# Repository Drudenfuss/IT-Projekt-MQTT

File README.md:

# IT-Projekt-MQTT
BZTG Oldenburg ETS 1. IT- Projekt MQTT Controller.

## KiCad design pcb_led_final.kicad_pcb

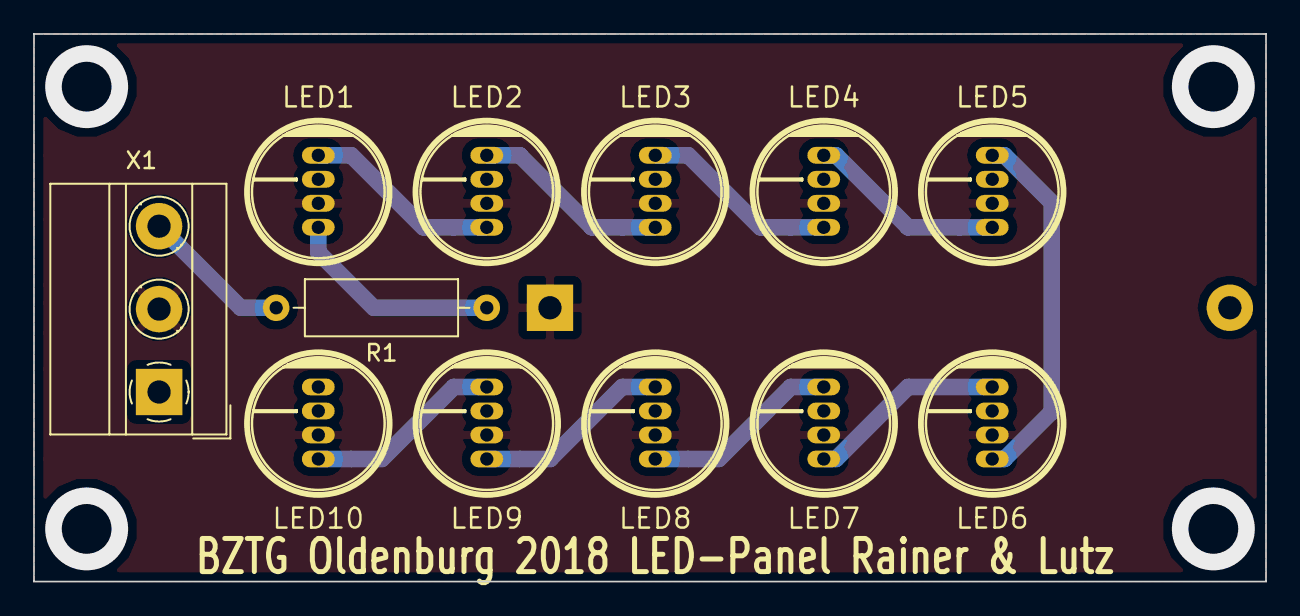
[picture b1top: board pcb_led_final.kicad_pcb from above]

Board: 2 copper layers, 74.3 x 33.0 mm, 13 parts (1 on the bottom side), 13 nets.

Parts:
C1: CP; CP_Axial_L34.5mm_D20.0mm_P41.00mm_Horizontal
LED1, LED2, LED3, LED4, LED5, LED6, LED7, LED8, LED9, LED10: WS2811; PL9823-SYSMATT-V4
R1: 220_Ohm; R_Axial_DIN0309_L9.0mm_D3.2mm_P12.70mm_Horizontal
X1: LED Terminal; TerminalBlock_MetzConnect_Type011_RT05503HBWC_1x03_P5.00mm_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

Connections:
/3.3V_VCC: C1.1, LED1.2, LED2.2, LED3.2, LED4.2, LED5.2, LED6.2, LED7.2, LED8.2, LED9.2, LED10.2, X1.2
/GND: C1.2, LED1.3, LED2.3, LED3.3, LED4.3, LED5.3, LED6.3, LED7.3, LED8.3, LED9.3, LED10.3, X1.1
unnamed: LED1.1, R1.1
unnamed: LED1.4, LED2.1
unnamed: LED2.4, LED3.1
unnamed: LED3.4, LED4.1
unnamed: LED4.4, LED5.1
unnamed: LED5.4, LED6.1
unnamed: LED6.4, LED7.1
unnamed: LED7.4, LED8.1
unnamed: LED8.4, LED9.1
unnamed: LED9.4, LED10.1
unnamed: R1.2, X1.3

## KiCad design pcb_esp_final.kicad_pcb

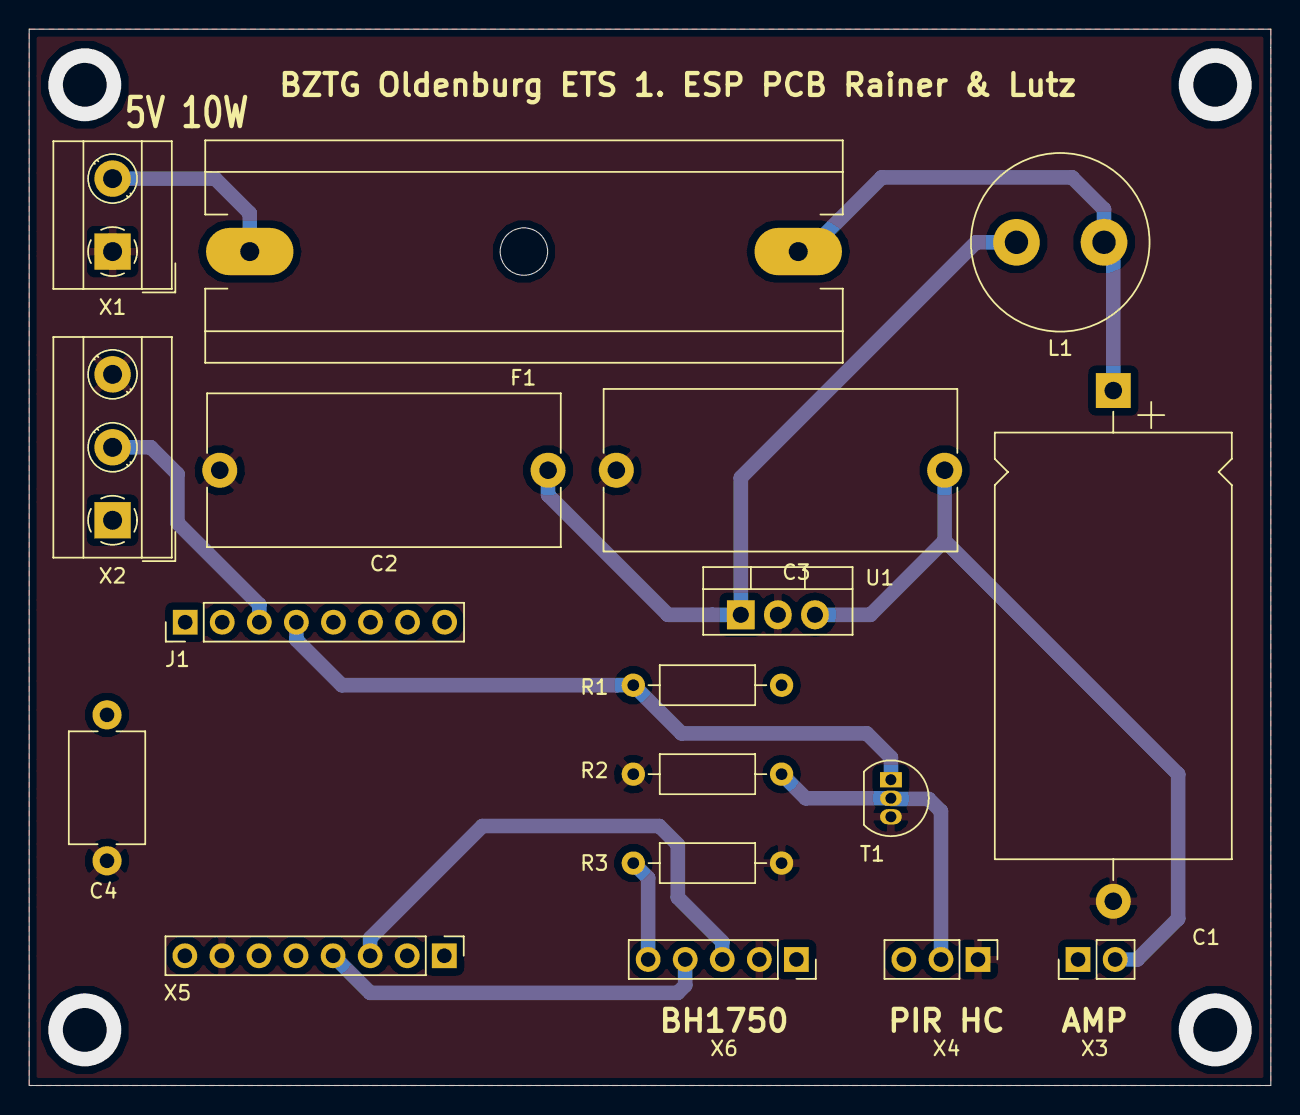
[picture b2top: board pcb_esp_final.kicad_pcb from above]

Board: 2 copper layers, 85.1 x 72.4 mm, 18 parts (0 on the bottom side), 12 nets.

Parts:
C1: 4,7 μF; CP_Axial_L29.0mm_D16.0mm_P35.00mm_Horizontal
C2: 10 μF; C_Rect_L24.0mm_W10.3mm_P22.50mm_MKT
C3: 22 μF; C_Rect_L24.0mm_W10.9mm_P22.50mm_MKT
C4: 100 nF; C_Disc_D7.5mm_W5.0mm_P10.00mm
F1: 3A_Mittelträge; Fuseholder_Cylinder-5x20mm_Schurter_0031-8002_Horizontal_Op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
J1: Conn_01x08_Male; PinHeader_1x08_P2.54mm_Vertical
L1: 12 μH; L_Radial_D12.0mm_P6.00mm_MuRATA_1900R
R1: 10K; R_Axial_DIN0207_L6.3mm_D2.5mm_P10.16mm_Horizontal
R2: 5K; R_Axial_DIN0207_L6.3mm_D2.5mm_P10.16mm_Horizontal
R3: 1K; R_Axial_DIN0207_L6.3mm_D2.5mm_P10.16mm_Horizontal
T1: BC413; TO-92_Inline
U1: AMSR01-783.3-NZ 3.3V; TO-220-3_Vertical
X1: USB_VCC; TerminalBlock_MetzConnect_Type055_RT01502HDWU_1x02_P5.00mm_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
X2: LED_Panel; TerminalBlock_MetzConnect_Type055_RT01503HDWU_1x03_P5.00mm_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
X3: Strommessung; PinHeader_1x02_P2.54mm_Vertical
X4: PIR-HC-SR501; PinHeader_1x03_P2.54mm_Vertical
X5: WeMos D1 Mini ESP 8266; PinHeader_1x08_P2.54mm_Vertical
X6: BH1750; PinSocket_1x05_P2.54mm_Vertical

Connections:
/3,3V_VCC: C4.1, J1.1, R1.2, X2.1, X3.1, X4.3, X6.1
/5V_VCC: F1.2, X1.2
/Addr: R3.1, X6.5
/D1: X5.3, X6.3
/D2: X5.4, X6.4
/D6: J1.4, R1.1, T1.1
/D7: J1.3, X2.2
/GND: C1.2, C2.2, C3.2, C4.2, R2.1, R3.2, T1.3, U1.2, X1.1, X2.3, X4.1, X5.7, X6.2
unnamed: C1.1, F1.1, L1.1
unnamed: C2.1, L1.2, U1.1
unnamed: C3.1, U1.3, X3.2
unnamed: R2.2, T1.2, X4.2

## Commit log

2018-12-19 Add files via upload
    Testsoftware Release
2019-01-07 Add files via upload
    Gehäuse DXF file
